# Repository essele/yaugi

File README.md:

# YAUGI -- Yet Another USB GPIB Interface

## Disclaimer

This is an experimental device and experimental code, it has not been 
fully tested and may damage your equipment. Please do not attempt to
use this device and code unless you know what you are doing.

I can accept no liability whatsoever for any damage caused.

## Introduction

Details to follow ... however:

The PCB KiCAD files are in the KiCAD directory

The code, which is a PSoC Creator project is in the "GPIB USB Adapter" directory.

This is work in progress and will be documented over time.

## Errata

The PCB is a test board and as such has a number of issues, most notibly:

- the shield of the IEE488 connector is not connected to the USB shield
- the IEE488 connector needs to be populated on the back of the board

The code is absoultely work-in-progress so lots of things won't work and
this will change over time.

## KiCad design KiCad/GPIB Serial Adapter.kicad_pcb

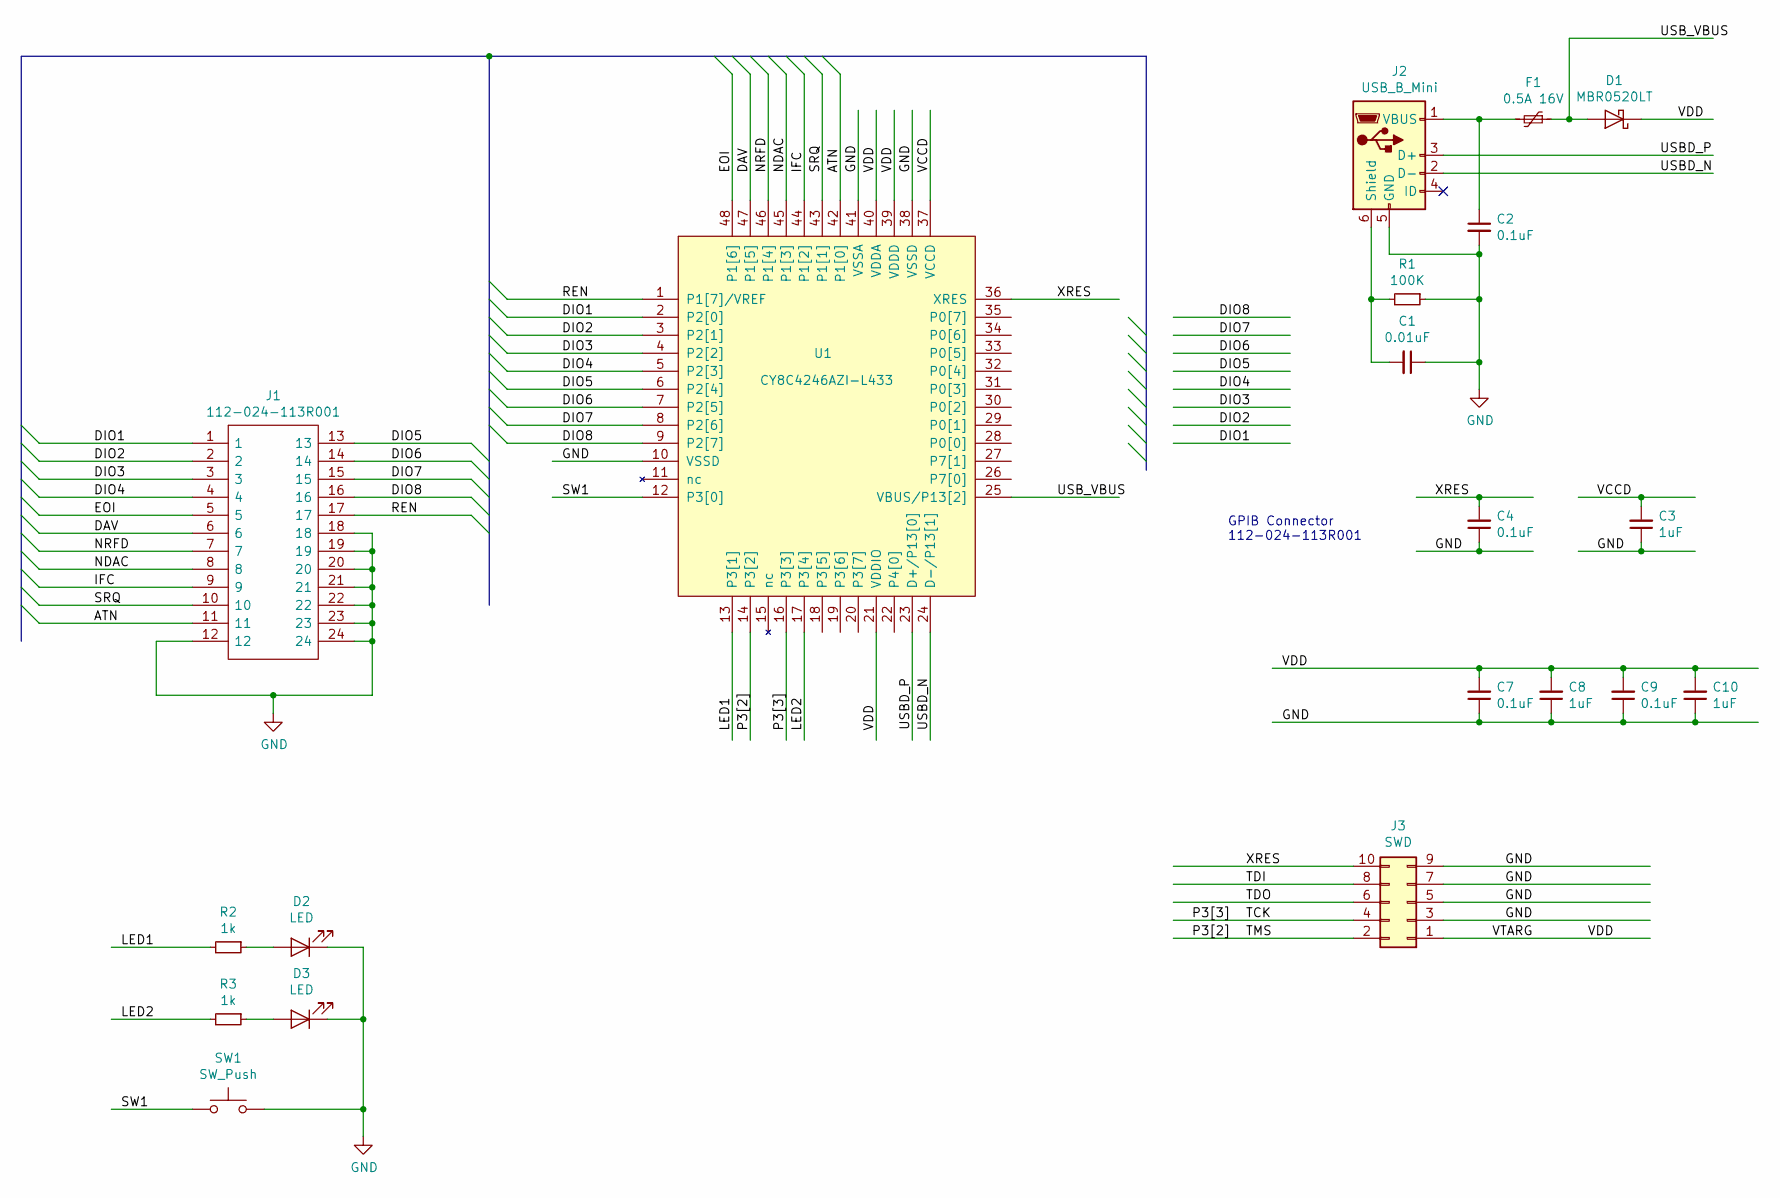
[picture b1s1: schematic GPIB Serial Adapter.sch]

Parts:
C1: 0.01uF; C_0603_HandSoldering
C2, C4, C7, C9: 0.1uF; C_0603_HandSoldering
C3, C8, C10: 1uF; C_0603_HandSoldering
D1: MBR0520LT; D_SOD-123
D2, D3: LED; LED_0805_HandSoldering
F1: 0.5A 16V; R_1210_HandSoldering
J1: 112-024-113R001; Manufacturer_Part_Number 112-024-113R001; Mouser Part Number 636-112-024-113R001
J2: USB_B_Mini; USB_Mini-B
J3: SWD; Pin_Header_Straight_2x05_Pitch1.27mm
R1: 100K; R_0805_HandSoldering
R2, R3: 1k; R_0603_HandSoldering
SW1: SW_Push; SW_PUSH_6mm_h8mm
U1: CY8C4246AZI-L433; LQFP-48_7x7mm_Pitch0.5mm

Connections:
/ATN: J1.11, U1.42 (P1[0])
/DAV: J1.6, U1.47 (P1[5])
/DIO1: J1.1, U1.2 (P2[0])
/DIO2: J1.2, U1.3 (P2[1])
/DIO3: J1.3, U1.4 (P2[2])
/DIO4: J1.4, U1.5 (P2[3])
/DIO5: J1.13, U1.6 (P2[4])
/DIO6: J1.14, U1.7 (P2[5])
/DIO7: J1.15, U1.8 (P2[6])
/DIO8: J1.16, U1.9 (P2[7])
/EOI: J1.5, U1.48 (P1[6])
/IFC: J1.9, U1.44 (P1[2])
/LED1: R2.2, U1.13 (P3[1])
/LED2: R3.2, U1.17 (P3[4])
/NDAC: J1.8, U1.45 (P1[3])
/NRFD: J1.7, U1.46 (P1[4])
/P3[2]: J3.2, U1.14 (P3[2])
/P3[3]: J3.4, U1.16 (P3[3])
/REN: J1.17, U1.1 (P1[7]/VREF)
/SRQ: J1.10, U1.43 (P1[1])
/SW1: SW1.1, U1.12 (P3[0])
/TDI: J3.8
/TDO: J3.6
/USBD_N: J2.2 (D-), U1.24 (D-/P13[1])
/USBD_P: J2.3 (D+), U1.23 (D+/P13[0])
/USB_VBUS: D1.2 (A), F1.1, U1.25 (VBUS/P13[2])
/VCCD: C3.2, U1.37 (VCCD)
/VDD: C7.2, C8.2, C9.2, C10.2, D1.1 (K), J3.1, U1.21 (VDDIO), U1.39 (VDDD), U1.40 (VDDA)
/XRES: C4.2, J3.10, U1.36 (XRES)
GND: C1.1, C2.2, C3.1, C4.1, C7.1, C8.1, C9.1, C10.1, D2.1 (K), D3.1 (K), J1.12, J1.18, J1.19, J1.20, J1.21, J1.22, J1.23, J1.24, J2.5 (GND), J3.3, J3.5, J3.7, J3.9, R1.1, SW1.2, U1.10 (VSSD), U1.38 (VSSD), U1.41 (VSSA)
unnamed: C1.2, J2.6 (Shield), R1.2
unnamed: C2.1, F1.2, J2.1 (VBUS)
unnamed: D2.2 (A), R2.1
unnamed: D3.2 (A), R3.1

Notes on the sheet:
GPIB Connector 112-024-113R001

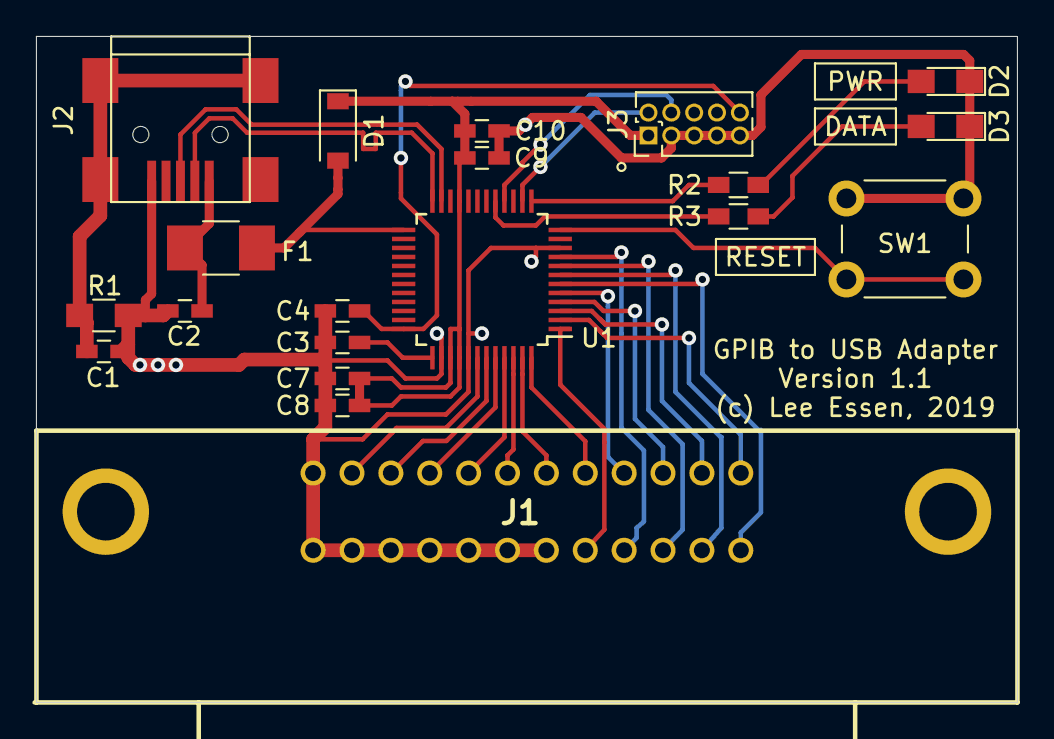
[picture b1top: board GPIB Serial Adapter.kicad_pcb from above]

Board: 2 copper layers, 54.5 x 37.0 mm, 20 parts (0 on the bottom side), 32 nets.

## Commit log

2019-10-19 testing commit
2019-10-19 added KiCad schematics and pcb
2019-10-19 bulk commit of current status for EEVBlog
2019-10-19 quick tweak
2019-10-19 Added a few more ++ commands
2019-10-25 Refactor to include tmc and composite support
2019-10-26 work on non-interactive, further tidy.
2019-10-26 Further cleanup, remove of filename conflicg for usb_tmc
2019-10-26 Tidy of interactive code
2019-10-27 Part implementation of USBTMC class requests
